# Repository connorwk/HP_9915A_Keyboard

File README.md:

# HP_9915A_Keyboard
Keyboard schematic for the HP 9915A keyboard

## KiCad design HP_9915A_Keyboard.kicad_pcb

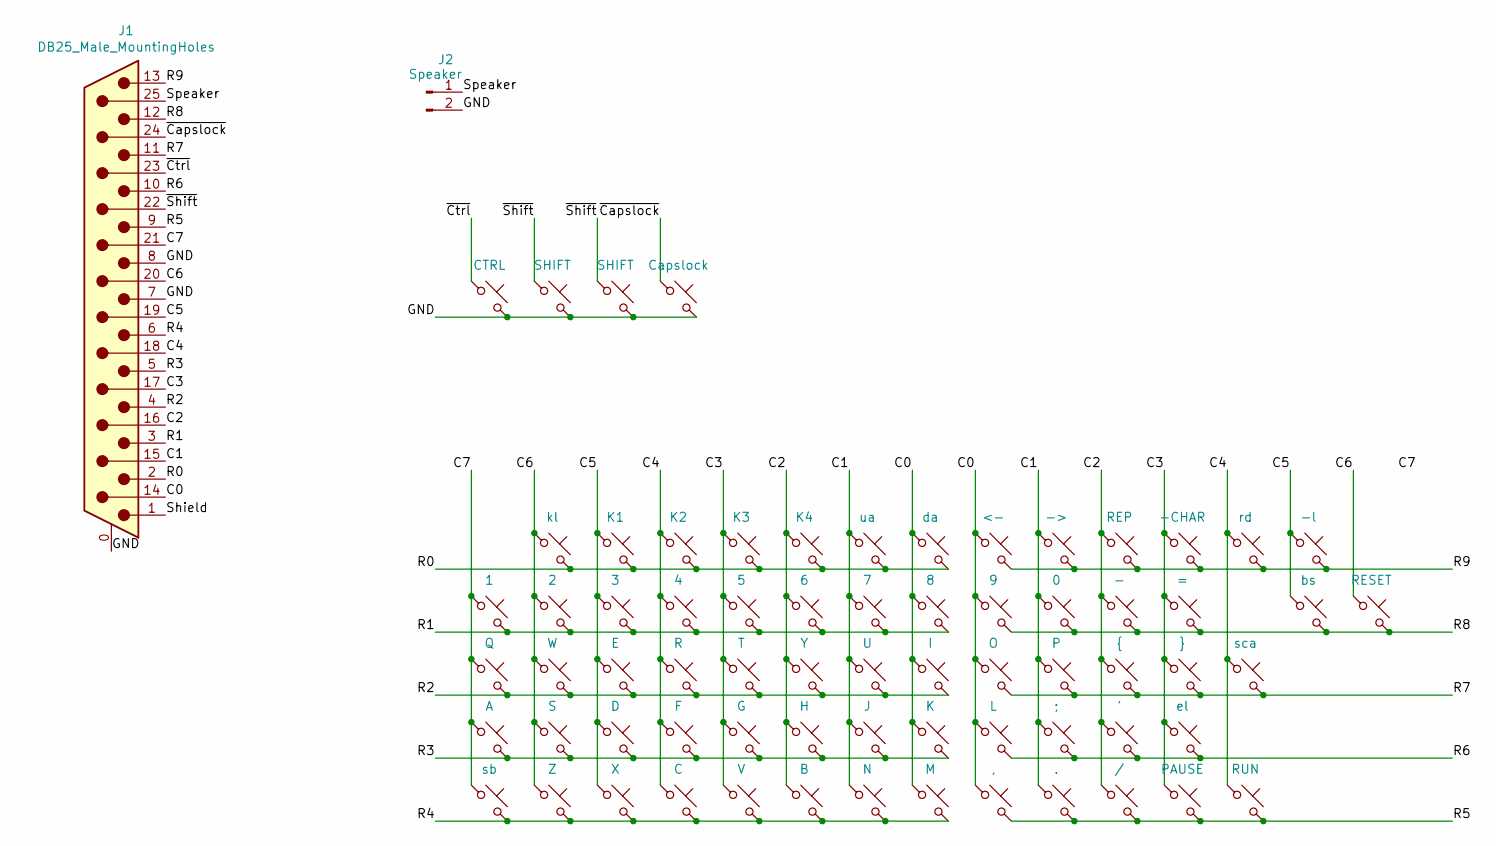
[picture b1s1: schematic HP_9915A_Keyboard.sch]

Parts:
J1: DB25_Male_MountingHoles; DSUB-25_Male_Horizontal_P2.77x2.84mm_EdgePinOffset14.56mm_H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
J2: Speaker; PinSocket_1x02_P2.54mm_Vertical
SW1: CTRL; SW_Cherry_MX_1.00u_PCB
SW2, SW3: SHIFT; SW_Cherry_MX_1.50u_PCB
SW4: Capslock; SW_Cherry_MX_1.00u_PCB
SW5: kl; SW_Cherry_MX_1.00u_PCB
SW6: K1; SW_Cherry_MX_1.50u_PCB
SW7: K2; SW_Cherry_MX_1.50u_PCB
SW8: K3; SW_Cherry_MX_1.50u_PCB
SW9: K4; SW_Cherry_MX_1.50u_PCB
SW10: ua; SW_Cherry_MX_1.00u_PCB
SW11: da; SW_Cherry_MX_1.00u_PCB
SW12: <-; SW_Cherry_MX_1.00u_PCB
SW13: ->; SW_Cherry_MX_1.00u_PCB
SW14: REP; SW_Cherry_MX_1.00u_PCB
SW15: -CHAR; SW_Cherry_MX_1.00u_PCB
SW16: rd; SW_Cherry_MX_1.00u_PCB
SW17: -l; SW_Cherry_MX_1.00u_PCB
SW18: 1; SW_Cherry_MX_1.00u_PCB
SW19: 2; SW_Cherry_MX_1.00u_PCB
SW20: 3; SW_Cherry_MX_1.00u_PCB
SW21: 4; SW_Cherry_MX_1.00u_PCB
SW22: 5; SW_Cherry_MX_1.00u_PCB
SW23: 6; SW_Cherry_MX_1.00u_PCB
SW24: 7; SW_Cherry_MX_1.00u_PCB
SW25: 8; SW_Cherry_MX_1.00u_PCB
SW26: 9; SW_Cherry_MX_1.00u_PCB
SW27: 0; SW_Cherry_MX_1.00u_PCB
SW28: -; SW_Cherry_MX_1.00u_PCB
SW29: =; SW_Cherry_MX_1.00u_PCB
SW31: bs; SW_Cherry_MX_1.00u_PCB
SW32: RESET; SW_Cherry_MX_1.00u_PCB
SW33: Q; SW_Cherry_MX_1.00u_PCB
SW34: W; SW_Cherry_MX_1.00u_PCB
SW35: E; SW_Cherry_MX_1.00u_PCB
SW36: R; SW_Cherry_MX_1.00u_PCB
SW37: T; SW_Cherry_MX_1.00u_PCB
SW38: Y; SW_Cherry_MX_1.00u_PCB
SW39: U; SW_Cherry_MX_1.00u_PCB
SW40: I; SW_Cherry_MX_1.00u_PCB
SW41: O; SW_Cherry_MX_1.00u_PCB
SW42: P; SW_Cherry_MX_1.00u_PCB
SW43: {; SW_Cherry_MX_1.00u_PCB
SW44: }; SW_Cherry_MX_1.00u_PCB
SW45: sca; SW_Cherry_MX_2.00u_PCB
SW46: A; SW_Cherry_MX_1.00u_PCB
SW47: S; SW_Cherry_MX_1.00u_PCB
SW48: D; SW_Cherry_MX_1.00u_PCB
SW49: F; SW_Cherry_MX_1.00u_PCB
SW50: G; SW_Cherry_MX_1.00u_PCB
SW51: H; SW_Cherry_MX_1.00u_PCB
SW52: J; SW_Cherry_MX_1.00u_PCB
SW53: K; SW_Cherry_MX_1.00u_PCB
SW54: L; SW_Cherry_MX_1.00u_PCB
SW55: ;; SW_Cherry_MX_1.00u_PCB
SW56: '; SW_Cherry_MX_1.00u_PCB
SW57: el; SW_Cherry_MX_2.00u_PCB
SW58: sb; SW_Cherry_MX_6.25u_PCB
SW59: Z; SW_Cherry_MX_1.00u_PCB
SW60: X; SW_Cherry_MX_1.00u_PCB
SW61: C; SW_Cherry_MX_1.00u_PCB
SW62: V; SW_Cherry_MX_1.00u_PCB
SW63: B; SW_Cherry_MX_1.00u_PCB
SW64: N; SW_Cherry_MX_1.00u_PCB
SW65: M; SW_Cherry_MX_1.00u_PCB
SW66: ,; SW_Cherry_MX_1.00u_PCB
SW67: .; SW_Cherry_MX_1.00u_PCB
SW68: /; SW_Cherry_MX_1.00u_PCB
SW69: PAUSE; SW_Cherry_MX_1.50u_PCB
SW70: RUN; SW_Cherry_MX_1.00u_PCB

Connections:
/C0: J1.14, SW11.1, SW12.1, SW25.1, SW26.1, SW40.1, SW41.1, SW53.1, SW54.1, SW65.1, SW66.1
/C1: J1.15, SW10.1, SW13.1, SW24.1, SW27.1, SW39.1, SW42.1, SW52.1, SW55.1, SW64.1, SW67.1
/C2: J1.16, SW9.1, SW14.1, SW23.1, SW28.1, SW38.1, SW43.1, SW51.1, SW56.1, SW63.1, SW68.1
/C3: J1.17, SW8.1, SW15.1, SW22.1, SW29.1, SW37.1, SW44.1, SW50.1, SW57.1, SW62.1, SW69.1
/C4: J1.18, SW7.1, SW16.1, SW21.1, SW36.1, SW45.1, SW49.1, SW61.1, SW70.1
/C5: J1.19, SW6.1, SW17.1, SW20.1, SW31.1, SW35.1, SW48.1, SW60.1
/C6: J1.20, SW5.1, SW19.1, SW32.1, SW34.1, SW47.1, SW59.1
/C7: J1.21, SW18.1, SW33.1, SW46.1, SW58.1
/GND: J1.0 (PAD), J1.7, J1.8, J2.2, SW1.2, SW2.2, SW3.2, SW4.2
/R0: J1.2, SW5.2, SW6.2, SW7.2, SW8.2, SW9.2, SW10.2, SW11.2
/R1: J1.3, SW18.2, SW19.2, SW20.2, SW21.2, SW22.2, SW23.2, SW24.2, SW25.2
/R2: J1.4, SW33.2, SW34.2, SW35.2, SW36.2, SW37.2, SW38.2, SW39.2, SW40.2
/R3: J1.5, SW46.2, SW47.2, SW48.2, SW49.2, SW50.2, SW51.2, SW52.2, SW53.2
/R4: J1.6, SW58.2, SW59.2, SW60.2, SW61.2, SW62.2, SW63.2, SW64.2, SW65.2
/R5: J1.9, SW66.2, SW67.2, SW68.2, SW69.2, SW70.2
/R6: J1.10, SW54.2, SW55.2, SW56.2, SW57.2
/R7: J1.11, SW41.2, SW42.2, SW43.2, SW44.2, SW45.2
/R8: J1.12, SW26.2, SW27.2, SW28.2, SW29.2, SW31.2, SW32.2
/R9: J1.13, SW12.2, SW13.2, SW14.2, SW15.2, SW16.2, SW17.2
/Shield: J1.1
/Speaker: J1.25, J2.1
/~Capslock: J1.24, SW4.1
/~Ctrl: J1.23, SW1.1
/~Shift: J1.22, SW2.1, SW3.1

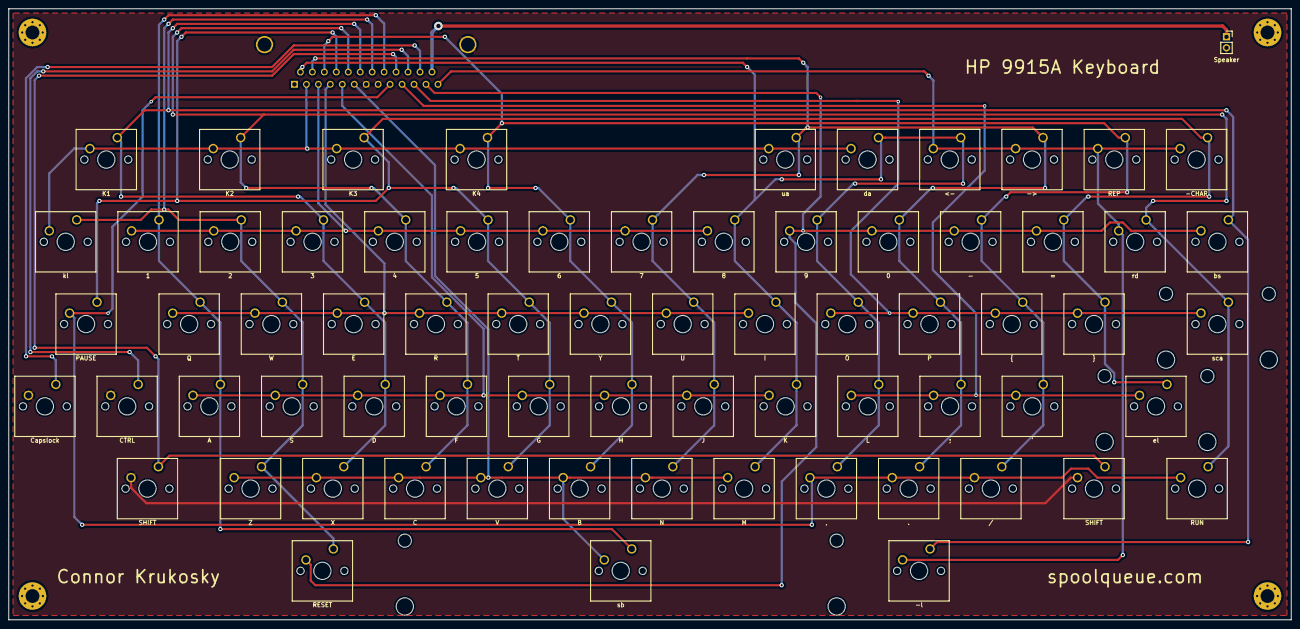
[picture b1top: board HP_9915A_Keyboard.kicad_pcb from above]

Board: 2 copper layers, 297.0 x 141.5 mm, 71 parts (1 on the bottom side), 23 nets.

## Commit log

2021-01-06 add gitignore
2021-01-06 Add kicad project and gerbers.
